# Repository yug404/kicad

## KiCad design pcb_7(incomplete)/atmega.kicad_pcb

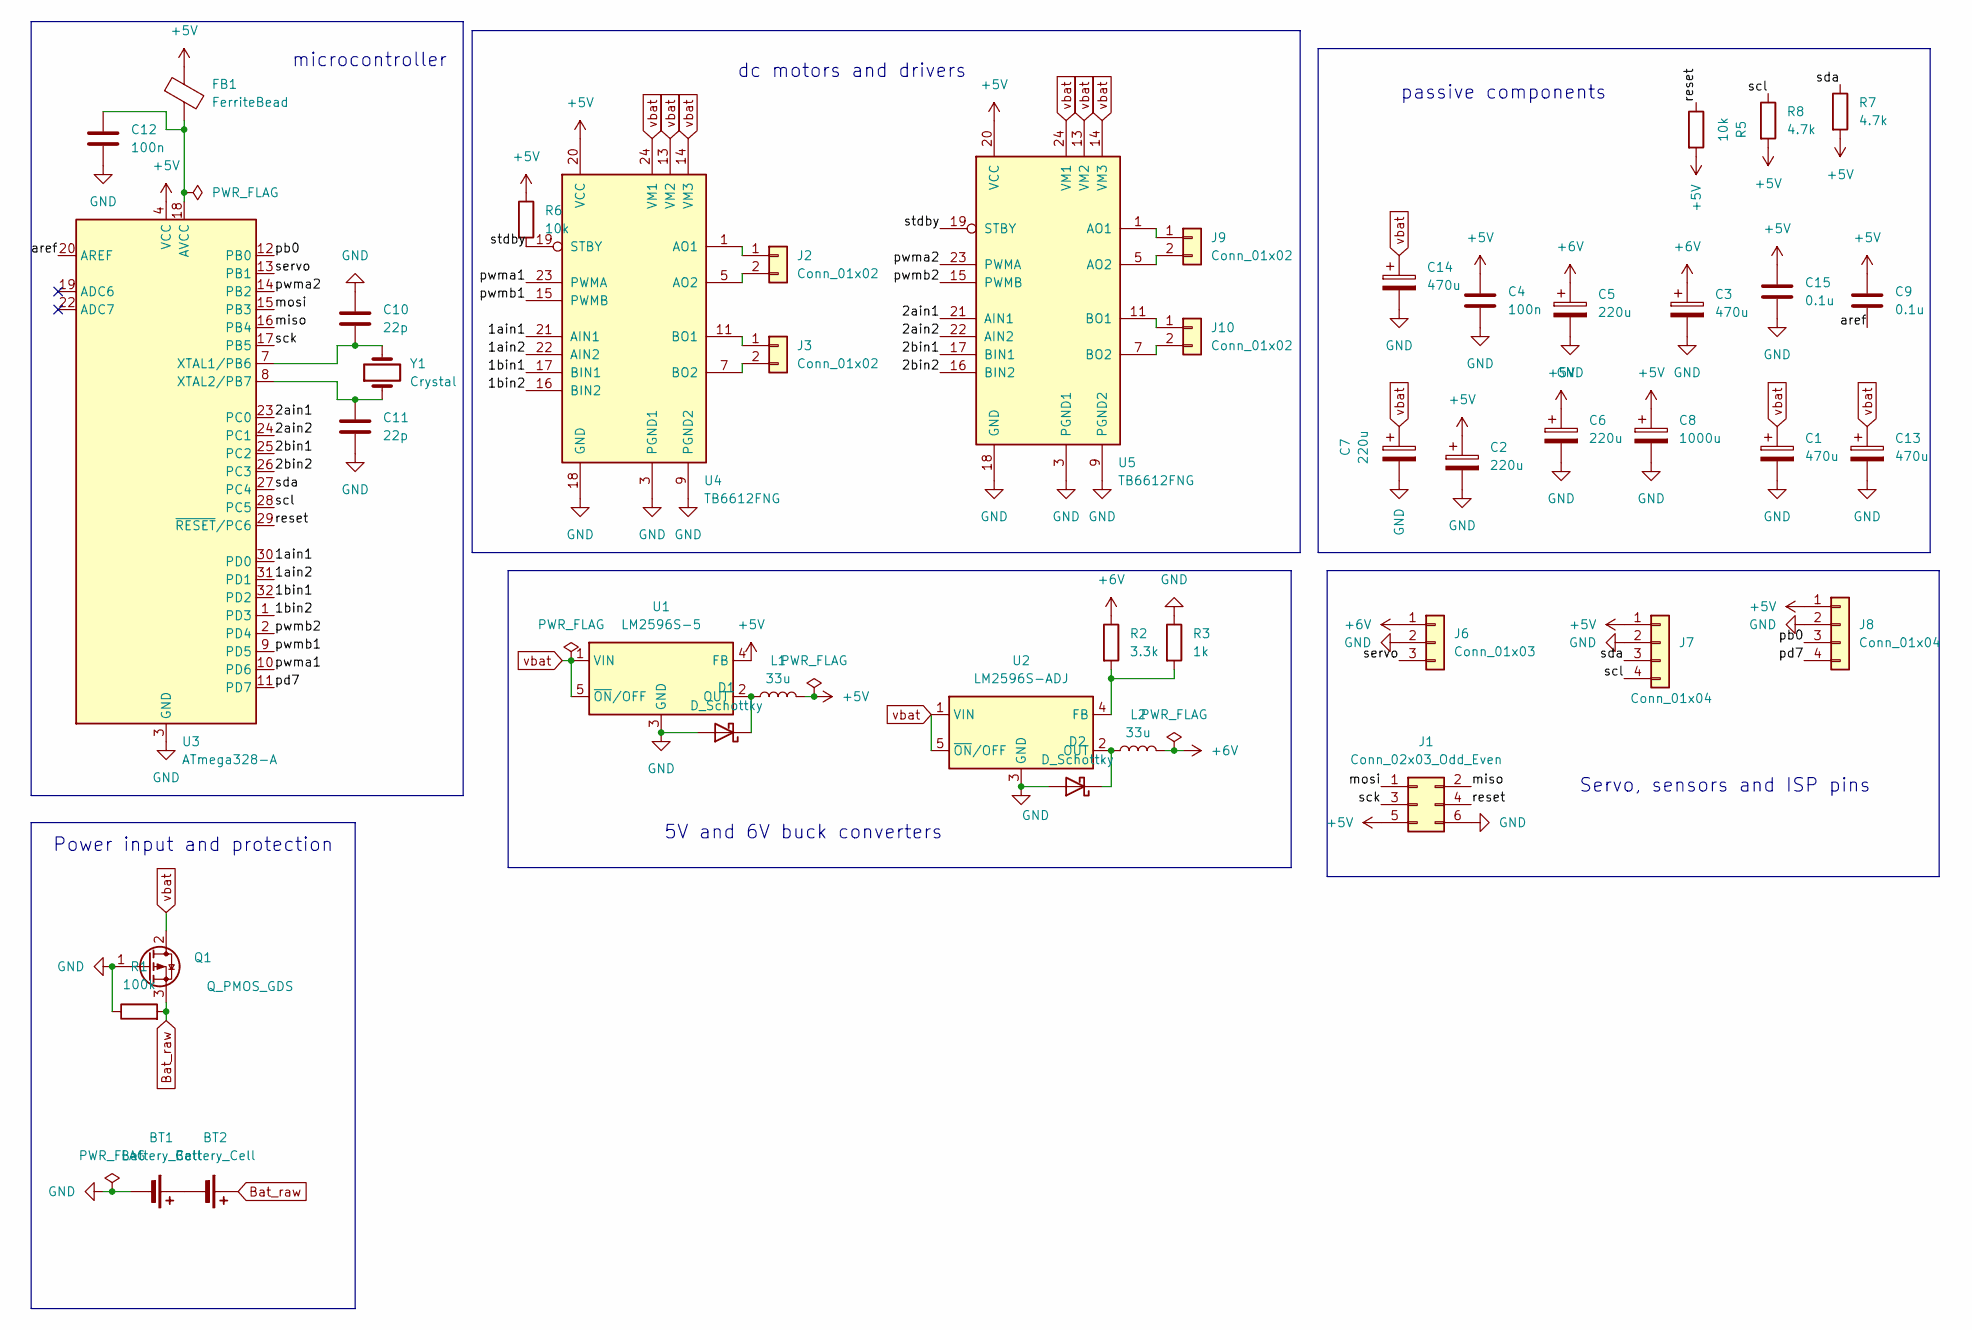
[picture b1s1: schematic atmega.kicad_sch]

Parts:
BT1, BT2: Battery_Cell; BatteryHolder_Keystone_1042_1x18650
C1, C3, C13, C14: 470u; CP_Elec_8x10
C2, C5, C6, C7: 220u; CP_Elec_8x10
C4, C12: 100n; C_0805_2012Metric
C8: 1000u; CP_Elec_8x10
C9, C15: 0.1u; C_0805_2012Metric
C10, C11: 22p; C_0805_2012Metric
D1, D2: D_Schottky; D_SMA
FB1: FerriteBead; R_0805_2012Metric
J1: Conn_02x03_Odd_Even; PinHeader_2x03_P2.54mm_Vertical
J2, J3, J9, J10: Conn_01x02; JST_PH_S2B-PH-K_1x02_P2.00mm_Horizontal
J6: Conn_01x03; PinHeader_1x03_P2.54mm_Vertical
J7, J8: Conn_01x04; PinHeader_1x04_P2.54mm_Vertical
L1, L2: 33u; L_10.4x10.4_H4.8
Q1: Q_PMOS_GDS; SOT-23
R1: 100k; R_0805_2012Metric
R2: 3.3k; R_0805_2012Metric
R3: 1k; R_0805_2012Metric
R5, R6: 10k; R_0805_2012Metric
R7, R8: 4.7k; R_0805_2012Metric
U1: LM2596S-5; TO-263-5_TabPin3
U2: LM2596S-ADJ; TO-263-5_TabPin3
U3: ATmega328-A; TQFP-32_7x7mm_P0.8mm
U4, U5: TB6612FNG; SSOP-24_5.3x8.2mm_P0.65mm
Y1: Crystal; Crystal_SMD_3225-4Pin_3.2x2.5mm

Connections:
+5V: C2.1, C4.1, C6.1, C8.1, C9.1, C15.1, FB1.1, J1.5, J7.1, J8.1, L1.2, R5.2, R6.1, R7.2, R8.2, U1.4 (FB), U3.4 (VCC), U3.6 (VCC), U4.20 (VCC), U5.20 (VCC)
+6V: C3.1, C5.1, J6.1, L2.2, R2.1
/1ain1: U3.30 (PD0), U4.21 (AIN1)
/1ain2: U3.31 (PD1), U4.22 (AIN2)
/1bin1: U3.32 (PD2), U4.17 (BIN1)
/1bin2: U3.1 (PD3), U4.16 (BIN2)
/2ain1: U3.23 (PC0), U5.21 (AIN1)
/2ain2: U3.24 (PC1), U5.22 (AIN2)
/2bin1: U3.25 (PC2), U5.17 (BIN1)
/2bin2: U3.26 (PC3), U5.16 (BIN2)
/aref: C9.2, U3.20 (AREF)
/miso: J1.2, U3.16 (PB4)
/mosi: J1.1, U3.15 (PB3)
/pb0: J8.3, U3.12 (PB0)
/pd7: J8.4, U3.11 (PD7)
/pwma1: U3.10 (PD6), U4.23 (PWMA)
/pwma2: U3.14 (PB2), U5.23 (PWMA)
/pwmb1: U3.9 (PD5), U4.15 (PWMB)
/pwmb2: U3.2 (PD4), U5.15 (PWMB)
/reset: J1.4, R5.1, U3.29 (~RESET/PC6)
/sck: J1.3, U3.17 (PB5)
/scl: J7.4, R8.1, U3.28 (PC5)
/sda: J7.3, R7.1, U3.27 (PC4)
/servo: J6.3, U3.13 (PB1)
/stdby: R6.2, U4.19 (STBY), U5.19 (STBY)
Bat_raw: BT2.1 (+), Q1.3 (S), R1.2
GND: BT1.2 (-), C1.2, C2.2, C3.2, C4.2, C5.2, C6.2, C7.2, C8.2, C10.1, C11.2, C12.2, C13.2, C14.2, C15.2, D1.2 (A), D2.2 (A), J1.6, J6.2, J7.2, J8.2, Q1.1 (G), R1.1, R3.1, U1.3 (GND), U2.3 (GND), U3.3 (GND), U3.5 (GND), U3.21 (GND), U4.3 (PGND1), U4.4 (PGND1), U4.9 (PGND2), U4.10 (PGND2), U4.18 (GND), U5.3 (PGND1), U5.4 (PGND1), U5.9 (PGND2), U5.10 (PGND2), U5.18 (GND)
unnamed: BT1.1 (+), BT2.2 (-)
unnamed: D1.1 (K), L1.1, U1.2 (OUT)
unnamed: D2.1 (K), L2.1, U2.2 (OUT)
unnamed: J2.1, U4.1 (AO1), U4.2 (AO1)
unnamed: J2.2, U4.5 (AO2), U4.6 (AO2)
unnamed: J3.1, U4.11 (BO1), U4.12 (BO1)
unnamed: J3.2, U4.7 (BO2), U4.8 (BO2)
unnamed: J9.1, U5.1 (AO1), U5.2 (AO1)
unnamed: J9.2, U5.5 (AO2), U5.6 (AO2)
unnamed: J10.1, U5.11 (BO1), U5.12 (BO1)
unnamed: J10.2, U5.7 (BO2), U5.8 (BO2)
unnamed: R2.2, R3.2, U2.4 (FB)
unnamed: C12.1, FB1.2, U3.18 (AVCC)
unnamed: C10.2, U3.7 (XTAL1/PB6), Y1.2
unnamed: C11.1, U3.8 (XTAL2/PB7), Y1.1
vbat: C1.1, C7.1, C13.1, C14.1, Q1.2 (D), U1.1 (VIN), U1.5 (~ON/OFF), U2.1 (VIN), U2.5 (~ON/OFF), U4.13 (VM2), U4.14 (VM3), U4.24 (VM1), U5.13 (VM2), U5.14 (VM3), U5.24 (VM1)

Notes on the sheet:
5V and 6V buck converters
Servo, sensors and ISP pins
dc motors and drivers
passive components
microcontroller
Power input and protection

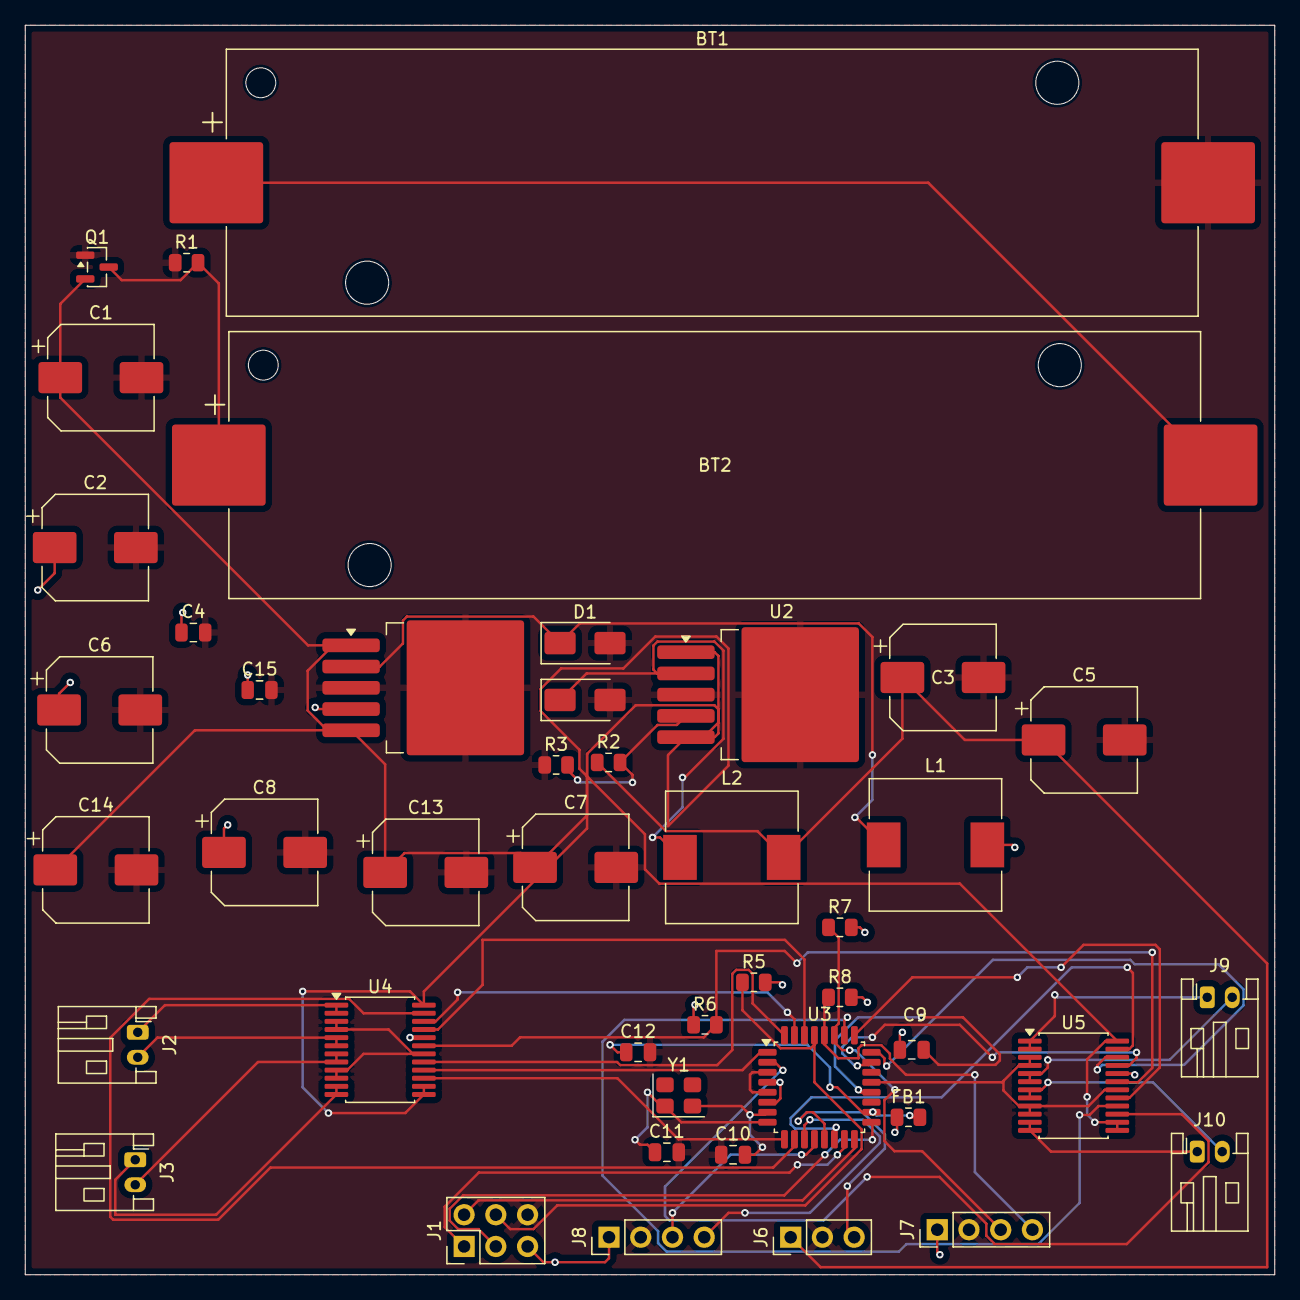
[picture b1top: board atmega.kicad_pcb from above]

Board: 2 copper layers, 100.0 x 100.0 mm, 44 parts (0 on the bottom side), 43 nets.

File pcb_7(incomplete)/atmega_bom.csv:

Reference	Qty	Value	DNP	Exclude from BOM	Exclude from Board	Footprint	Datasheet
BT1,BT2	2	Battery_Cell				Battery:BatteryHolder_Keystone_1042_1x18650	~
C1,C3,C13,C14	4	470u				Capacitor_SMD:CP_Elec_8x10	~
C2,C5,C6,C7	4	220u				Capacitor_SMD:CP_Elec_8x10	~
C4,C12	2	100n				Capacitor_SMD:C_0805_2012Metric	~
C8	1	1000u				Capacitor_SMD:CP_Elec_8x10	~
C9,C15	2	0.1u				Capacitor_SMD:C_0805_2012Metric	~
C10,C11	2	22p				Capacitor_SMD:C_0805_2012Metric	~
D1,D2	2	D_Schottky				Diode_SMD:D_SMA	~
FB1	1	FerriteBead				Resistor_SMD:R_0805_2012Metric	~
J1	1	Conn_02x03_Odd_Even				Connector_PinHeader_2.54mm:PinHeader_2x03_P2.54mm_Vertical	~
J2,J3,J9,J10	4	Conn_01x02				Connector_JST:JST_PH_S2B-PH-K_1x02_P2.00mm_Horizontal	~
J6	1	Conn_01x03				Connector_PinHeader_2.54mm:PinHeader_1x03_P2.54mm_Vertical	~
J7,J8	2	Conn_01x04				Connector_PinHeader_2.54mm:PinHeader_1x04_P2.54mm_Vertical	~
L1,L2	2	33u				Inductor_SMD:L_10.4x10.4_H4.8	~
Q1	1	Q_PMOS_GDS				Package_TO_SOT_SMD:SOT-23	~
R1	1	100k				Resistor_SMD:R_0805_2012Metric	~
R2	1	3.3k				Resistor_SMD:R_0805_2012Metric	~
R3	1	1k				Resistor_SMD:R_0805_2012Metric	~
R5,R6	2	10k				Resistor_SMD:R_0805_2012Metric	~
R7,R8	2	4.7k				Resistor_SMD:R_0805_2012Metric	~
U1	1	LM2596S-5				Package_TO_SOT_SMD:TO-263-5_TabPin3	http://www.ti.com/lit/ds/symlink/lm2596.pdf
U2	1	LM2596S-ADJ				Package_TO_SOT_SMD:TO-263-5_TabPin3	http://www.ti.com/lit/ds/symlink/lm2596.pdf
U3	1	ATmega328-A				Package_QFP:TQFP-32_7x7mm_P0.8mm	http://ww1.microchip.com/downloads/en/DeviceDoc/ATmega328_P%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
U4,U5	2	TB6612FNG				Package_SO:SSOP-24_5.3x8.2mm_P0.65mm	https://toshiba.semicon-storage.com/us/product/linear/motord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
Y1	1	Crystal				Crystal:Crystal_SMD_3225-4Pin_3.2x2.5mm	~

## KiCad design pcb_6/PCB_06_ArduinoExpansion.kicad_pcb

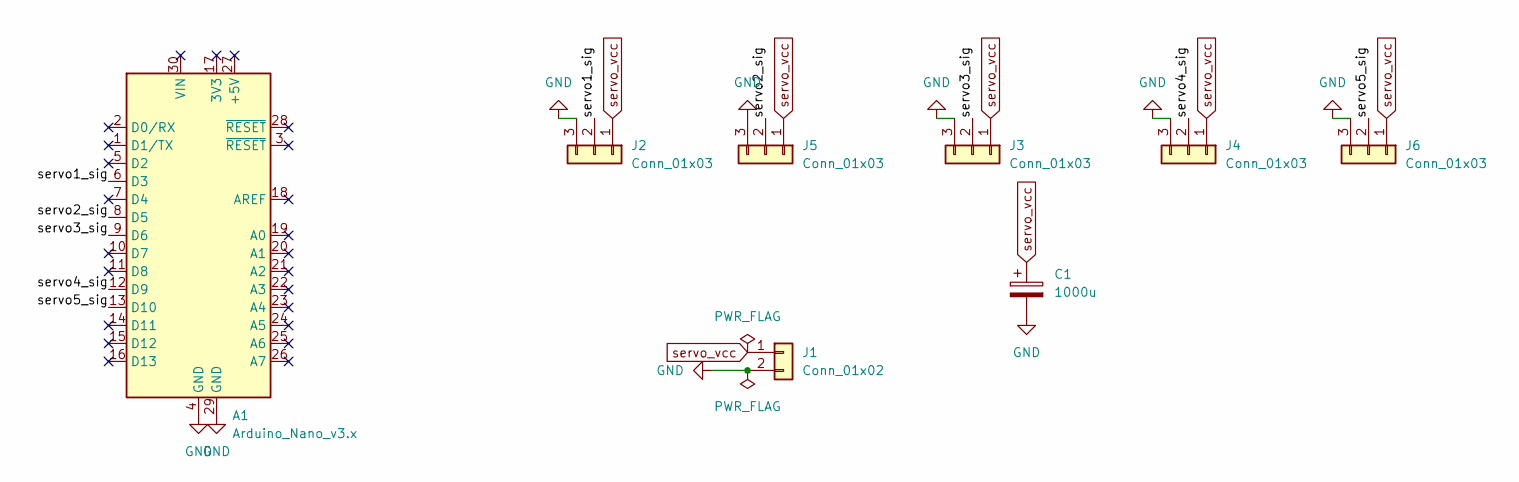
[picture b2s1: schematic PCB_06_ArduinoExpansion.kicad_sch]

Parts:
A1: Arduino_Nano_v3.x; Arduino_Nano
C1: 1000u; CP_Radial_D8.0mm_P3.50mm
J1: Conn_01x02; PinHeader_1x02_P2.54mm_Vertical
J2, J3, J4, J5, J6: Conn_01x03; PinHeader_1x03_P2.54mm_Vertical

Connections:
/servo1_sig: A1.6 (D3), J2.2
/servo2_sig: A1.8 (D5), J5.2
/servo3_sig: A1.9 (D6), J3.2
/servo4_sig: A1.12 (D9), J4.2
/servo5_sig: A1.13 (D10), J6.2
GND: A1.4 (GND), A1.29 (GND), C1.2, J1.2, J2.3, J3.3, J4.3, J5.3, J6.3
servo_vcc: C1.1, J1.1, J2.1, J3.1, J4.1, J5.1, J6.1

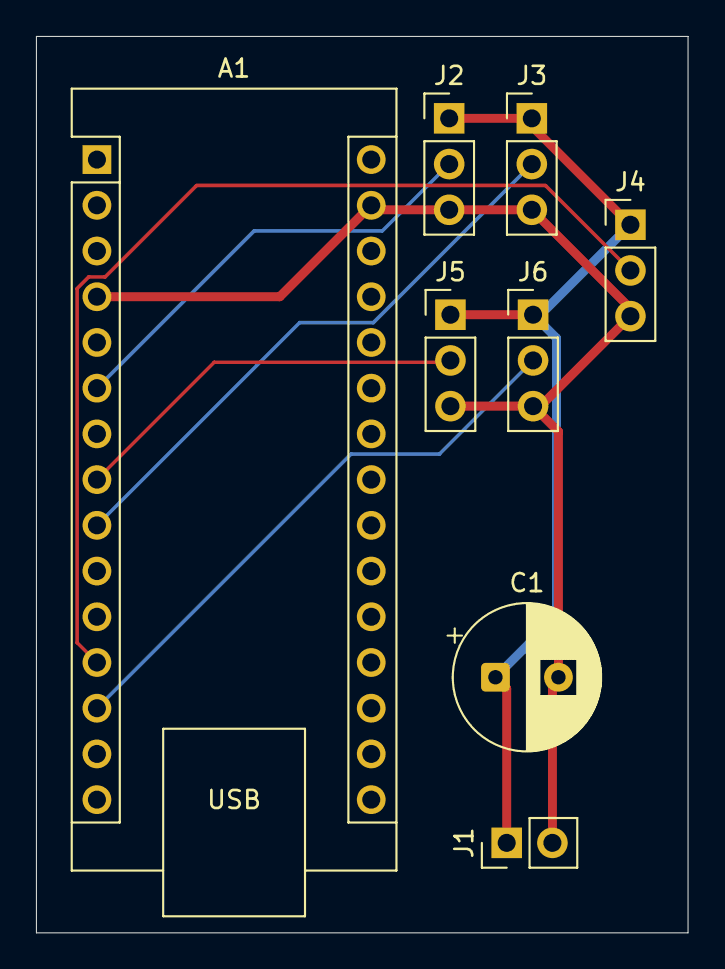
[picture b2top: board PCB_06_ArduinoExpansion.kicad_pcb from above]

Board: 2 copper layers, 36.2 x 49.8 mm, 8 parts (0 on the bottom side), 7 nets.

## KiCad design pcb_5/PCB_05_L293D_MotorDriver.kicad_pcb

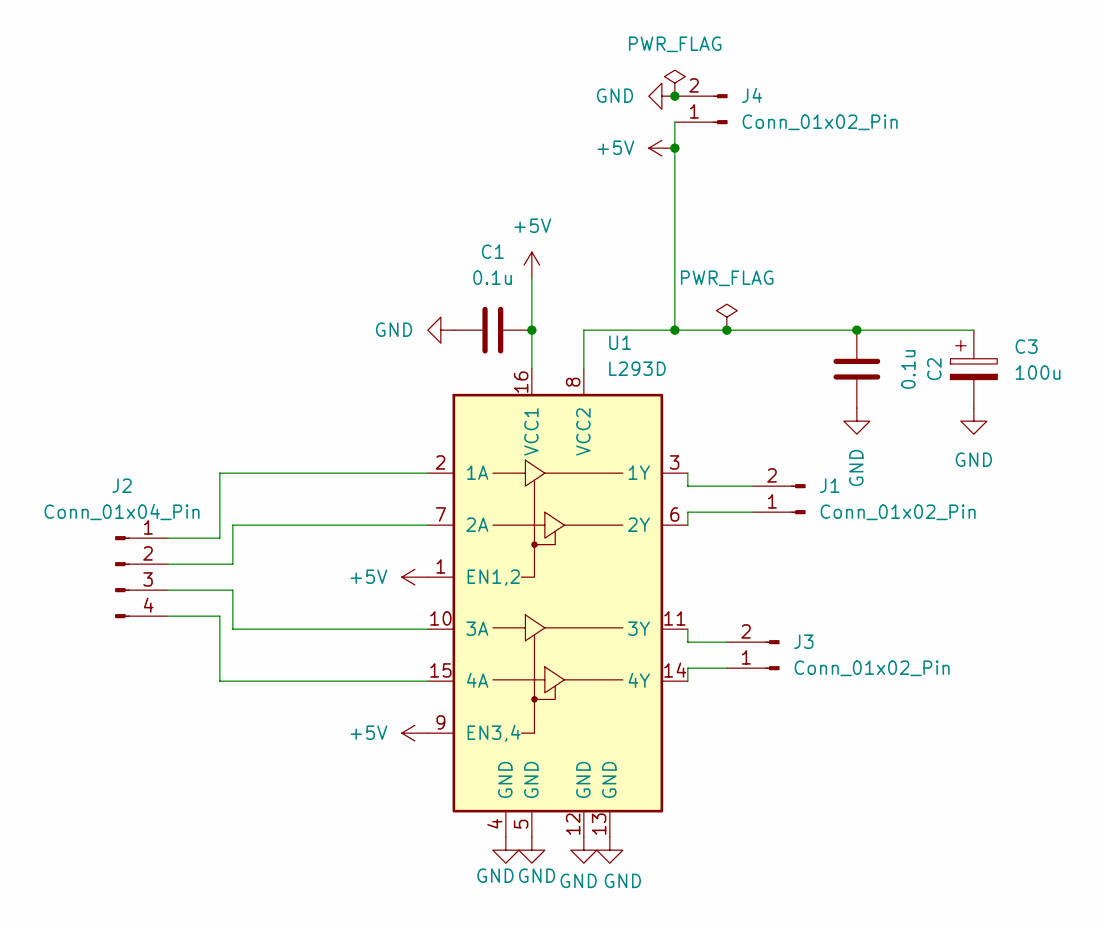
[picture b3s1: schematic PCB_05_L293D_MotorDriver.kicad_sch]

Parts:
C1, C2: 0.1u; C_Disc_D5.0mm_W2.5mm_P2.50mm
C3: 100u; CP_Radial_D5.0mm_P2.00mm
J1, J3, J4: Conn_01x02_Pin; PinHeader_1x02_P2.54mm_Vertical
J2: Conn_01x04_Pin; PinHeader_1x04_P2.54mm_Vertical
U1: L293D; DIP-16_W7.62mm

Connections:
+5V: C1.2, C2.1, C3.1, J4.1, U1.1 (EN1,2), U1.8 (VCC2), U1.9 (EN3,4), U1.16 (VCC1)
GND: C1.1, C2.2, C3.2, J4.2, U1.4 (GND), U1.5 (GND), U1.12 (GND), U1.13 (GND)
unnamed: J1.1, U1.6 (2Y)
unnamed: J1.2, U1.3 (1Y)
unnamed: J2.1, U1.2 (1A)
unnamed: J2.2, U1.7 (2A)
unnamed: J2.3, U1.10 (3A)
unnamed: J2.4, U1.15 (4A)
unnamed: J3.1, U1.14 (4Y)
unnamed: J3.2, U1.11 (3Y)

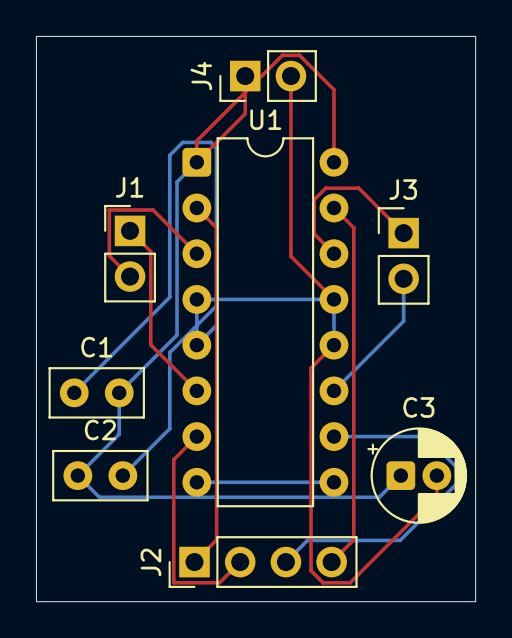
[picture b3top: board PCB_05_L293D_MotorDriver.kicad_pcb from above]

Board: 2 copper layers, 24.4 x 31.4 mm, 8 parts (0 on the bottom side), 10 nets.

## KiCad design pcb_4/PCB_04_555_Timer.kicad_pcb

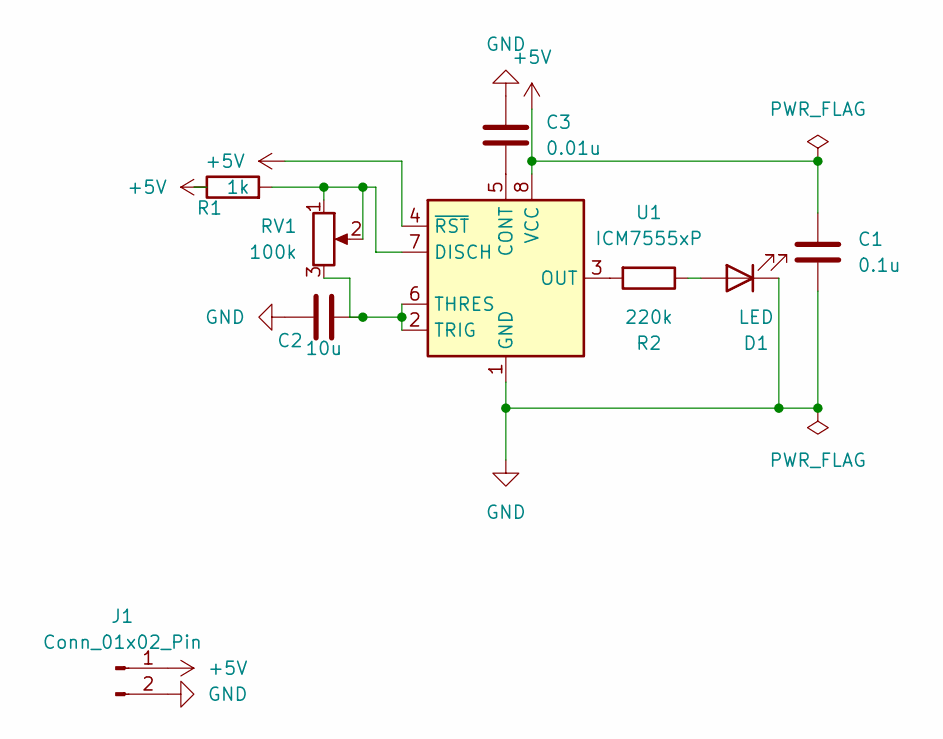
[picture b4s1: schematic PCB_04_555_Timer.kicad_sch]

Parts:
C1: 0.1u; C_Disc_D5.0mm_W2.5mm_P2.50mm
C2: 10u; CP_Radial_D5.0mm_P2.00mm
C3: 0.01u; C_Disc_D5.0mm_W2.5mm_P2.50mm
D1: LED; LED_D5.0mm
J1: Conn_01x02_Pin; PinHeader_1x02_P2.54mm_Vertical
R1: 1k; R_Axial_DIN0207_L6.3mm_D2.5mm_P7.62mm_Horizontal
R2: 220k; R_Axial_DIN0207_L6.3mm_D2.5mm_P7.62mm_Horizontal
RV1: 100k; Potentiometer_Bourns_3386P_Vertical
U1: ICM7555xP; DIP-8_W7.62mm

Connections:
+5V: C1.1, J1.1, R1.1, U1.4 (~RST), U1.8 (VCC)
GND: C1.2, C2.1, C3.1, D1.1 (K), J1.2, U1.1 (GND)
unnamed: D1.2 (A), R2.1
unnamed: C3.2, U1.5 (CONT)
unnamed: R1.2, RV1.1, RV1.2, U1.7 (DISCH)
unnamed: R2.2, U1.3 (OUT)
unnamed: C2.2, RV1.3, U1.2 (TRIG), U1.6 (THRES)

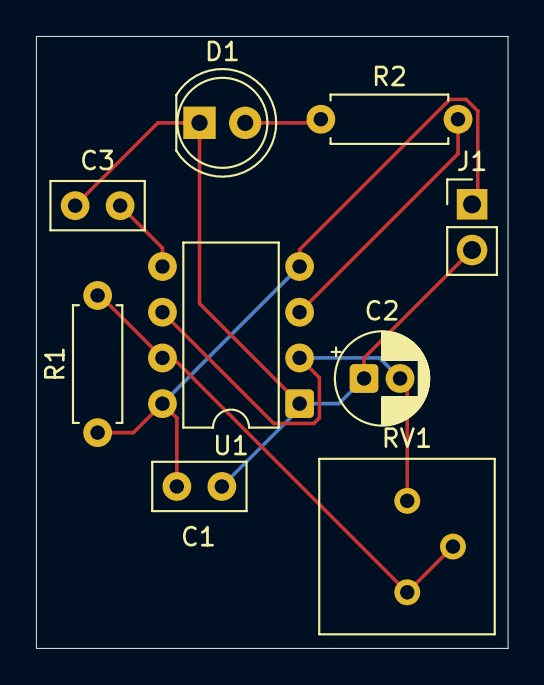
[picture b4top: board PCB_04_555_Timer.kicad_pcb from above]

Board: 2 copper layers, 26.2 x 34.0 mm, 9 parts (0 on the bottom side), 7 nets.

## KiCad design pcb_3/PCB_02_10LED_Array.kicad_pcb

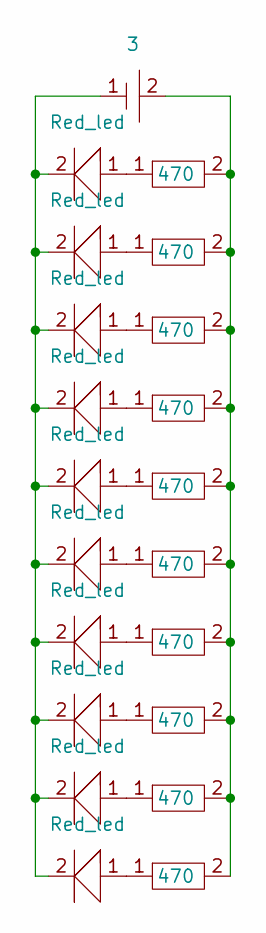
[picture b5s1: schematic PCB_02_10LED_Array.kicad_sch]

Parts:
U1: 3; BatteryHolder_Keystone_1060_1x2032
U2, U5, U7, U9, U11, U17, U18, U19, U20, U21: 470; Resistor_Axial_7p5mm_Custom
U3, U4, U6, U8, U10, U12, U13, U14, U15, U16: Red_led; customLED_5mm

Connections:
unnamed: U1.1, U3.2, U4.2, U6.2, U8.2, U10.2, U12.2, U13.2, U14.2, U15.2, U16.2
unnamed: U1.2, U2.2, U5.2, U7.2, U9.2, U11.2, U17.2, U18.2, U19.2, U20.2, U21.2
unnamed: U2.1, U3.1
unnamed: U4.1, U5.1
unnamed: U6.1, U7.1
unnamed: U8.1, U9.1
unnamed: U10.1, U11.1
unnamed: U12.1, U17.1
unnamed: U13.1, U18.1
unnamed: U14.1, U19.1
unnamed: U15.1, U20.1
unnamed: U16.1, U21.1

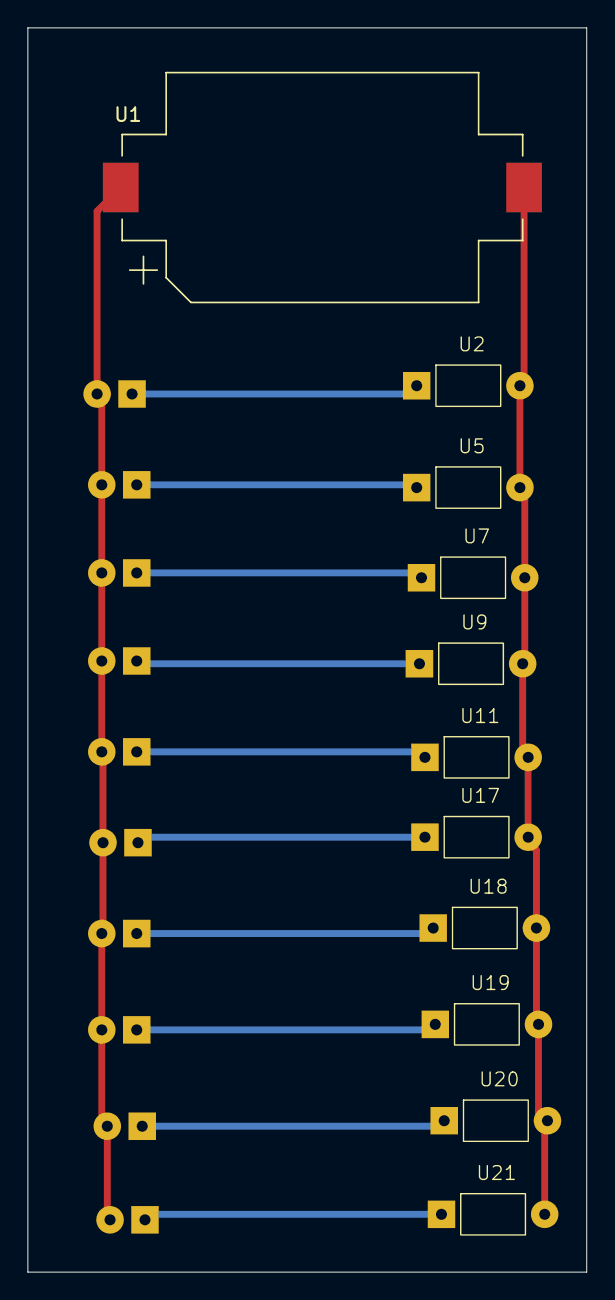
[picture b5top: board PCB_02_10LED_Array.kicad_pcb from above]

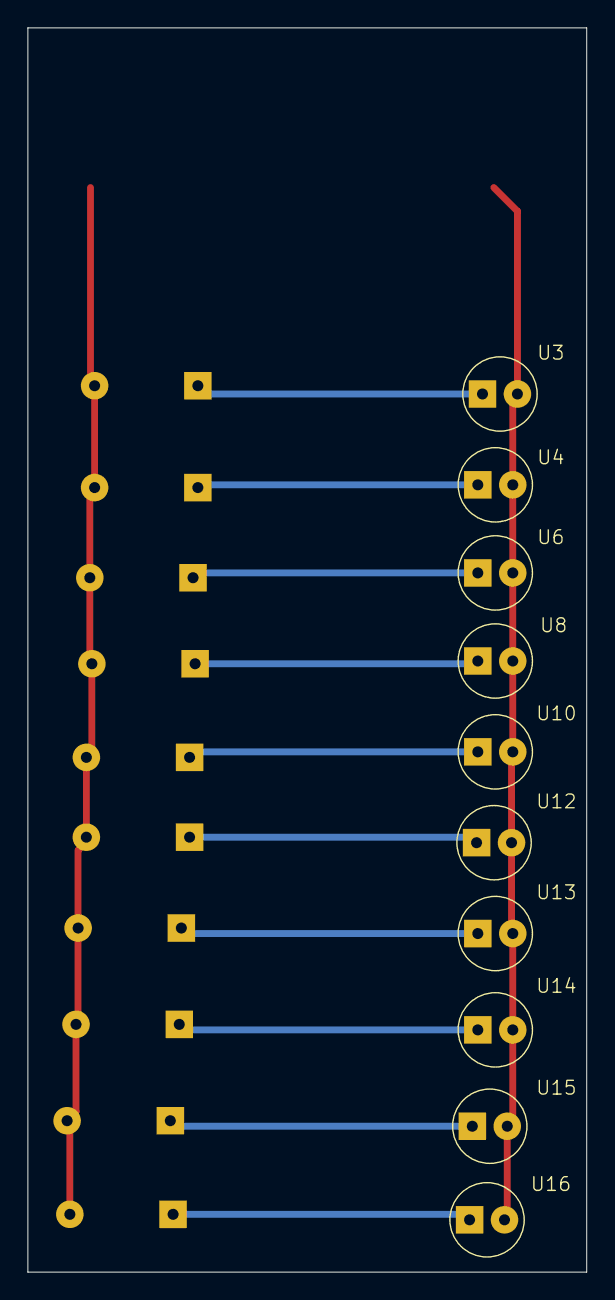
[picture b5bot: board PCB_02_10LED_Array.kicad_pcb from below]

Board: 2 copper layers, 40.6 x 90.4 mm, 21 parts (10 on the bottom side), 12 nets.

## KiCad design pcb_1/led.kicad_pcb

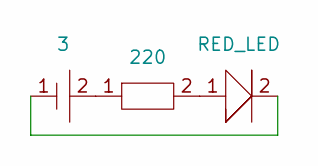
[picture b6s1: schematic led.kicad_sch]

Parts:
U1: 3; BatteryHolder_Keystone_1060_1x2032
U2: 220; Resistor_Axial_7p5mm_Custom
U3: RED_LED; customLED_5mm

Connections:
unnamed: U1.1, U3.2
unnamed: U1.2, U2.1
unnamed: U2.2, U3.1

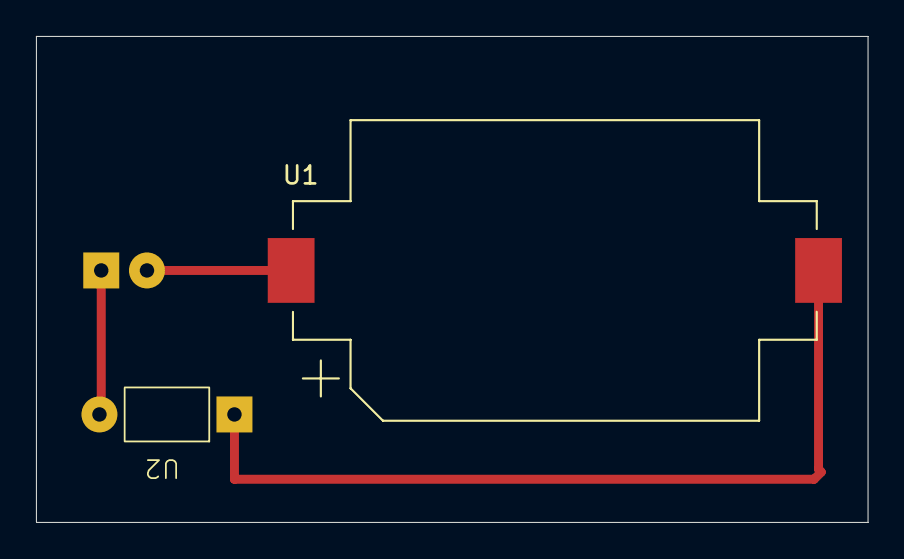
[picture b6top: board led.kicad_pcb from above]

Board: 2 copper layers, 46.2 x 27.0 mm, 3 parts (1 on the bottom side), 3 nets.
